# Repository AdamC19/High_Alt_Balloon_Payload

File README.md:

# High-Altitude Balloon Payload

These are the source files for my high-altitude balloon payload. 

Read more about this project and its development [on my website](http://acordingley.us/ke8itf/).

The primary goals of the payload are:
* Make measurements and collect data: 
    * GPS Location
    * Barometric pressure (second determination of altitude)
    * Temperature.
* Telemeter the data via the Amatuer Radio 2m band (144.39MHz).
* Log the data to non-volatile storage.
* Powered from NiMH batteries.

The primary goal of the real-time telemetry is to be able to receive GPS coordinates so that we can track the balloon and hopefully chase it and find it more easily. The payload will also include a self-contained camera to take pictures. 

## Hardware Block Diagrams
### Logical Overview

### Power Architecture

### 2m Radio Transmitter

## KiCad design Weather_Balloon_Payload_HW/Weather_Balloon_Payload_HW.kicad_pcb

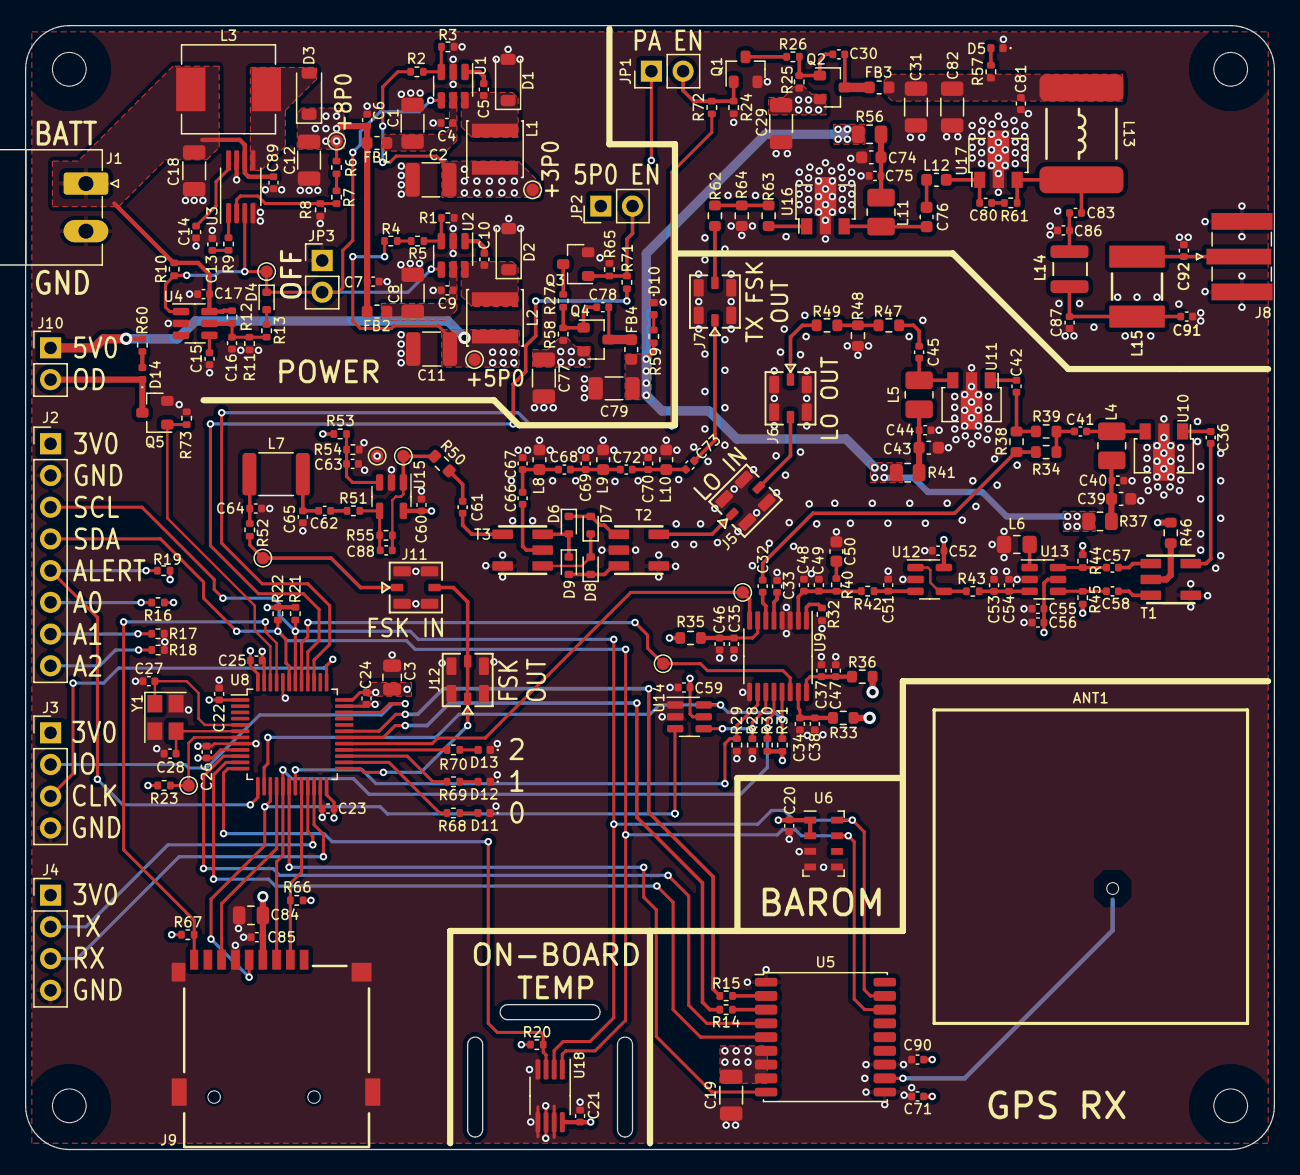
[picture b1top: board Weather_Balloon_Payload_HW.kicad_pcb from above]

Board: 4 copper layers, 100.0 x 90.0 mm, 254 parts (0 on the bottom side), 142 nets.

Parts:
ANT1: GP.1575.25.4.A.02; Taoglas_GP.1575.25.4.A.02
C1, C8, C12, C18, C19, C29, C31, C77, C79, C82: 10uF; C_1206_3216Metric
C2, C11: 22uF; C_1210_3225Metric
C3, C84: 4.7uF; C_0805_2012Metric
C4, C6, C7, C9, C17, C20, C21, C22, C23, C24, C25, C26, C38, C46, C47, C48, C49, C51, C52, C56, C59, C60, C61, C62, C63, C80, C85, C89: 0.1uF; C_0402_1005Metric
C5, C10, C14, C15: 0.01uF; C_0402_1005Metric
C13, C16: 1500pF; C_0402_1005Metric
C27, C28, C91, C92: 18pF; C_0402_1005Metric
C30, C34, C35, C36, C37, C40, C41, C42, C44, C45, C53, C55, C57, C58, C71, C75, C78, C81, C83, C90: 1000pF; C_0402_1005Metric
C32, C33, C54, C88: 100pF; C_0402_1005Metric
C39, C43, C50, C74, C76: 2.2uF; C_0603_1608Metric
C64, C65: 150pF; C_0402_1005Metric
C66, C73: 12pF; C_0402_1005Metric
C67, C69, C70: 110pF; C_0402_1005Metric
C68, C72: 4.7pF; C_0402_1005Metric
C86, C87: 10pF; C_0402_1005Metric
D1, D2, D3: LMBR130T1G; D_SOD-123
D4: 1N4148WT; D_SOD-523
D5, D10, D11, D12, D13, D14: BLUE; LED_0402_1005Metric
D6, D7, D8, D9: SMS3922-079LF; D_SOD-523
FB1, FB2, FB3, FB4: 120@100MHz; L_0603_1608Metric
H1, H2, H3, H4: M2.5; MountingHole_2.7mm_M2.5
J1: Conn_01x02; PhoenixContact_MC_1,5_2-G-3.81_1x02_P3.81mm_Horizontal
J2: Conn_01x08; PinHeader_1x08_P2.54mm_Vertical
J3, J4: Conn_01x04; PinHeader_1x04_P2.54mm_Vertical
J5, J6, J7, J11, J12: MM8430-2610; Connector_Murata_MM8430-2610RA1
J8: Conn_Coaxial; SMA_Amphenol_132384_EdgeMount
J9: XKTF-015-G; microSD_Card_Socket_Generic
J10: Conn_01x02; PinHeader_1x02_P2.54mm_Vertical
JP1, JP2, JP3: Jumper_2_Open; PinHeader_1x02_P2.54mm_Vertical
L1, L2: 4.7uH; L_Sunlord_SWPA4018S
L3: 10uH; L_Sunlord_MWSA0624S
L4, L5, L11: 120nH; L_1008_2520Metric_Pad1.43x2.20mm_HandSolder
L6: 180nH; L_0805_2012Metric_Pad1.15x1.40mm_HandSolder
L7: 15uH; L_1812_4532Metric
L8, L9, L10: 9.1nH; L_0603_1608Metric
L12: 5.6nH; L_0603_1608Metric
L13: 180nH; L_Coilcraft_2222SQ-181
L14: 47nH; L_Coilcraft_1111SQ-47N
L15: 68nH; L_Coilcraft_1515SQ-68N
Q1, Q3, Q5: Si2302; SOT-23
Q2, Q4: Si2301; SOT-23
R1, R8, R9, R12, R19, R20, R24, R25, R58, R65, R66, R67, R73: 10k; R_0402_1005Metric
R2, R4: 47k; R_0402_1005Metric
R3: 16.2k; R_0402_1005Metric
R5, R7, R23, R28, R29, R30, R31: 4.7k; R_0402_1005Metric
R6: 49.9k; R_0402_1005Metric
R10, R11: 100k; R_0402_1005Metric
R13: 1M; R_0402_1005Metric
R14, R15, R68, R69, R70: 100; R_0402_1005Metric
R16, R17, R18, R44, R45, R53, R54, R57, R71, R72: 1k; R_0402_1005Metric
R21, R22, R61: 1.5k; R_0402_1005Metric
R26, R27, R42, R55: 324; R_0402_1005Metric
R32: 5.1k; R_0402_1005Metric
R33, R35, R36, R46, R62, R63, R64: 0.0; R_0603_1608Metric
R34, R38, R39, R50: 49.9; R_0603_1608Metric
R37, R41, R56: 1.8; R_0805_2012Metric
R40, R43, R51, R52: 220; R_0402_1005Metric
R47, R49: 8.2; R_0603_1608Metric
R48: 150; R_0603_1608Metric
R59, R60: 470; R_0402_1005Metric
T1: CX2045LNLT; XFMR_Pulse_CX2049LNLT
T2, T3: TC2-72T+; XFMR_Mini-Circuits_TC2-72T+
TP1, TP2, TP3, TP4, TP5, TP6, TP7, TP8, TP9, TP10: TestPoint; TestPoint_Pad_D1.0mm
U1, U2: AP3211K; SOT-23-6
U3: ADP1612; MSOP-8_3x3mm_P0.65mm
U4: NCP308SN180T1G; SOT-23-6
U5: MAX-M8C; ublox_MAX
U6: MS5607-02BA; LGA-8_3x5mm_P1.25mm
U8: STM32F334C8Tx; LQFP-48_7x7mm_P0.5mm
U9: ADF4002BRUZ; TSSOP-16_4.4x5mm_P0.65mm
U10, U11, U16: PGA-105; SOT-89-3
U12: TLV9061; TSOT-23-5
U13: MAX2606; SOT-23-6
U14: TS5A3159ADBVR; SOT-23-6
U15: ADA4891-1; TSOT-23-5
U17: PHA13-HLN+; SOT-89-3
U18: MCP9808_MSOP; MSOP-8_3x3mm_P0.65mm
Y1: 12MHz; Crystal_SMD_3225-4Pin_3.2x2.5mm

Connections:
5P0_EN: R71.1, U8.40 (PB4)
+3V0: C2.1, C3.1, C19.2, C20.2, C21.2, C22.1, C23.1, C24.1, C25.1, C26.1, C52.1, C55.2, C56.1, C59.1, C60.1, C71.2, C84.1, C85.1, C90.2, J2.1, J3.1, J4.1, J9.4 (VDD), JP1.1 (A), JP2.1 (A), L1.2, R2.2, R16.2, R19.1, R20.1, R21.2, R22.2, R23.2, R30.2, R31.2, R33.2, R35.2, R36.2, R44.1, R45.1, R46.2, R53.1, R66.1, R67.1, TP3.1, U5.6 (V_BCKP), U5.7 (VCC_IO), U5.8 (VCC), U6.1 (VDD), U6.2 (PS), U8.1 (VBAT), U8.9 (VDDA), U8.24 (VDD), U8.36 (VDD), U8.48 (VDD), U12.5 (V+), U13.5 (VCC), U14.5 (V+), U15.5 (V+), U18.8 (V_{DD})
+5V: C11.1, C77.1, J10.1, L2.2, Q4.2 (S), R4.2, R58.1, R60.1, TP4.1
+8V: C6.1, C7.1, C12.1, C29.1, D3.1 (K), FB1.1, FB2.1, Q2.2 (S), R6.1, R25.1, TP2.1
/GPS and Barometer/GPS_ANT_CONN: ANT1.1 (A), U5.11 (RF_IN)
/GPS and Barometer/TSNS_EXT_A0: J2.6, R16.1
/GPS and Barometer/TSNS_EXT_A1: J2.7, R17.1
/GPS and Barometer/TSNS_EXT_A2: J2.8, R18.1
/GPS and Barometer/UART_GPS_MCU_PROT: R15.2, U5.2 (TXD)
/GPS and Barometer/UART_MCU_GPS_PROT: R14.2, U5.3 (RXD)
/LO Generator/AVDD: C35.2, C46.1, R35.1, U9.7 (AVDD)
/LO Generator/DVDD: C34.2, C38.1, R33.1, U9.15 (DVDD)
/LO Generator/LOOP_FILT_BUF: R43.2, U12.1, U12.4 (-)
/LO Generator/LOOP_FILT_OUT: C51.1, R42.1, U12.3 (+)
/LO Generator/LOOP_FILT_RC: C50.1, R40.1
/LO Generator/LO_AMP_IN: C42.1, U11.1
/LO Generator/LO_AMP_OUT: C45.2, L5.2, U11.3
/LO Generator/LO_INTER: J5.2 (OUT), J6.2 (OUT)
/LO Generator/LO_PREAMP: C42.2, R38.2, R39.1
/LO Generator/LO_T_ATTN: R47.2, R48.2, R49.1
/LO Generator/LO_T_ATTN_IN: C45.1, R47.1
/LO Generator/LO_T_ATTN_OUT: J6.1 (IN), R49.2
/LO Generator/PLL_CLK: R28.2, U9.11 (CLK), U14.4
/LO Generator/PLL_CP_OUT: C48.1, C49.1, R40.2, R42.2, U9.2 (CP)
/LO Generator/PLL_RFIN: C32.2, R34.1, R38.1
/LO Generator/PLL_RFINA: C32.1, U9.6 (RFINA)
/LO Generator/PLL_RFINB: C33.1, U9.5 (RFINB)
/LO Generator/PLL_RSET: R32.1, U9.1 (RSET)
/LO Generator/RF_SE: C36.2, T1.4
/LO Generator/RF_SE_AMP_IN: C36.1, U10.1
/LO Generator/RF_SE_AMP_O: C41.2, L4.2, U10.3
/LO Generator/RF_SE_AMP_PWR: C39.1, C40.2, L4.1, R37.1
/LO Generator/RF_SE_DIV_IN: C41.1, R34.2, R39.2
/LO Generator/VCO_BALUN_CT: R46.1, T1.2
/LO Generator/VCO_IND: L6.2, U13.1 (IND)
/LO Generator/VCO_OUT_N: C58.1, R45.2, U13.4 (OUT-)
/LO Generator/VCO_OUT_P: C57.1, R44.2, U13.6 (OUT+)
/LO Generator/VCO_TUNE: C53.1, C54.1, R43.1, U13.3 (TUNE)
/LO Generator/VP_3V3: C37.2, C47.1, R36.1, U9.16 (VP)
/Microcontroller/BUZZ_LED_LOW: D14.1 (K), J10.2, Q5.3 (D)
/Microcontroller/BUZZ_LED_R: D14.2 (A), R60.2
/Microcontroller/DBG_RX: J4.3, U8.22 (PB11)
/Microcontroller/DBG_TX: J4.2, U8.21 (PB10)
/Microcontroller/HRTIM_CHC1: J11.2 (OUT), J12.1 (IN), J12.2 (OUT), U8.25 (PB12)
/Microcontroller/LED_0: R68.2, U8.26 (PB13)
/Microcontroller/LED_0_A: D11.2 (A), R68.1
/Microcontroller/LED_1: R69.2, U8.27 (PB14)
/Microcontroller/LED_1_A: D12.2 (A), R69.1
/Microcontroller/LED_2: R70.2, U8.28 (PB15)
/Microcontroller/LED_2_A: D13.2 (A), R70.1
/Microcontroller/OSC_IN: C27.2, U8.5 (PF0), Y1.1
/Microcontroller/OSC_OUT: C28.2, U8.6 (PF1), Y1.3
/Microcontroller/STM_RSTB: R23.1, TP5.1, U8.7 (NRST)
/Microcontroller/SWDCLK: J3.3, U8.37 (PA14)
/Microcontroller/SWDIO: J3.2, U8.34 (PA13)
/Power/5P0_EN_LED: D10.2 (A), R59.2
/Power/5P0_EN_NFET_G: JP2.2 (B), Q3.1 (G), R65.1, R71.2
/Power/5P0_NFET_D: Q3.3 (D), R27.2
/Power/5P0_PFET_G: C78.1, Q4.1 (G), R27.1, R58.2
/Power/BATT_VIN: C17.1, C18.1, C89.2, J1.1, L3.1, R10.2, R12.1, U3.6 (VIN), U4.6 (VDD)
/Power/BST_3P0: C5.2, U1.1 (BS)
/Power/BST_5P0: C10.2, U2.1 (BS)
/Power/COMP_8P0: R9.1, U3.1 (COMP)
/Power/COMP_8P0_RC: C13.1, R9.2
/Power/FB_3P0: R2.1, R3.1, U1.3 (FB)
/Power/FB_5P0: R1.1, R5.2, U2.3 (FB)
/Power/FB_8P0: R7.1, R8.1, U3.2 (FB)
/Power/FB_R_5P0: R4.1, R5.1
/Power/FB_R_8P0: R6.2, R7.2
/Power/PA_EN_LED: D5.2 (A), R57.2
/Power/PA_EN_NFET_D: Q1.3 (D), R26.2
/Power/PA_EN_NFET_G: JP1.2 (B), Q1.1 (G), R24.1, R72.2
/Power/PA_PFET_G: C30.1, Q2.1 (G), R25.2, R26.1
/Power/SS_8P0: C14.1, U3.8 (SS)
/Power/SW_3P0: C5.1, D1.1 (K), L1.1, U1.6 (SW)
/Power/SW_5P0: C10.1, D2.1 (K), L2.1, U2.6 (SW)
/Power/SW_8P0: D3.2 (A), L3.2, U3.5 (SW)
/Power/SW_OUT_5P0: C78.2, FB4.1, Q4.3 (D)
/Power/SW_OUT_8P0: C30.2, FB3.1, Q2.3 (D)
/Power/UVLO_DLY_CAP: C15.1, U4.4 (CT)
/Power/UVLO_HYST: D4.2 (A), R13.2
/Power/UVLO_RSTB: D4.1 (K), JP3.2 (B), R10.1, TP1.1, U1.4 (EN), U2.4 (EN), U3.3 (EN), U4.1 (~RESET)
/Power/UVLO_SNS: C16.1, R11.2, R12.2, R13.1, U4.5 (SENSE)
/Power/VIN_3P0: C1.1, C4.1, FB1.2, U1.5 (IN)
/Power/VIN_5P0: C8.1, C9.1, FB2.2, U2.5 (IN)
/Transmitter/ANT_CONN: C92.2, J8.1 (In), L15.2
/Transmitter/ANT_MATCH: C83.1, C86.1, L14.1
/Transmitter/ANT_MATCH_2: C87.1, C91.2, L14.2, L15.1
/Transmitter/BASEBAND: C88.2, R50.2, R55.1, TP7.1, U15.1
/Transmitter/BASE_FILT_50: C61.1, R50.1
/Transmitter/DBM_1: D6.1 (K), D7.2 (A), T2.3
/Transmitter/DBM_2: D7.1 (K), D8.2 (A), T3.3
/Transmitter/DBM_3: D8.1 (K), D9.2 (A), T2.1
/Transmitter/DBM_4: D6.2 (A), D9.1 (K), T3.1
/Transmitter/MIX_FILT_1: C66.1, C67.1, C68.2, L8.1
/Transmitter/MIX_FILT_2: C68.1, C69.1, C72.2, L9.1
/Transmitter/MIX_FILT_3: C70.1, C72.1, C73.2, L10.1
/Transmitter/MIX_IF_OUT: C66.2, T3.2
/Transmitter/MIX_RF_IN: C61.2, T3.6
/Transmitter/PA_AMP_IN: C80.1, L12.2, U17.1
/Transmitter/PA_AMP_IN_1: C76.1, L12.1
/Transmitter/PA_RC: C80.2, R61.2
/Transmitter/PA_RF_DC: C83.2, L13.2, R61.1, U17.3
/Transmitter/PWM_FILT_AC: C62.2, R51.2
/Transmitter/PWM_FILT_IN: C64.2, L7.1, R52.1
/Transmitter/PWM_FILT_OUT: C62.1, C65.2, L7.2
/Transmitter/RF_TX_AMP_OUT: C76.2, L11.2, U16.3
/Transmitter/RF_TX_ATTN_OUT: R63.2, U16.1
/Transmitter/RF_TX_MOD: J7.2 (OUT), R62.1
/Transmitter/RF_TX_MOD_TP: C73.1, J7.1 (IN)
/Transmitter/RF_TX_T_ATTN: R62.2, R63.1, R64.2
/Transmitter/U15_INN: C88.1, R51.1, R55.2, U15.4 (-)
/Transmitter/U15_INP: C63.2, R53.2, R54.1, U15.3 (+)
BUZZ_LED_EN: Q5.1 (G), R73.1, U8.46 (PB9)
GND: C1.2, C2.2, C3.2, C4.2, C6.2, C7.2, C8.2, C9.2, C11.2, C12.2, C13.2, C14.2, C15.2, C16.2, C17.2, C18.2, C19.1, C20.1, C21.1, C22.2, C23.2, C24.2, C25.2, C26.2, C27.1, C28.1, C29.2, C31.2, C33.2, C34.1, C35.1, C37.1, C38.2, C39.2, C40.1, C43.2, C44.1, C46.2, C47.2, C48.2, C49.2, C50.2, C51.2, C52.2, C53.2, C54.2, C55.1, C56.2, C59.2, C60.2, C63.1, C64.1, C65.1, C67.2, C69.2, C70.2, C71.1, C74.2, C75.1, C77.2, C79.2, C81.1, C82.2, C84.2, C85.2, C86.2, C87.2, C89.1, C90.1, C91.1, C92.1, D1.2 (A), D2.2 (A), D5.1 (K), D10.1 (K), D11.1 (K), D12.1 (K), D13.1 (K), J1.2, J2.2, J3.4, J4.4, J5.3 (GND), J6.3 (GND), J7.3 (GND), J8.2 (Ext), J9.6 (VSS), J9.10 (SHIELD), J11.3 (GND), J12.3 (GND), JP3.1 (A), L6.1, L8.2, L9.2, L10.2, Q1.2 (S), Q3.2 (S), Q5.2 (S), R1.2, R3.2, R8.2, R11.1, R17.2, R18.2, R24.2, R28.1, R29.1, R32.2, R48.1, R54.2, R64.1, R65.2, R73.2, T1.6, T2.2, T2.6, T3.4, TP8.1, U1.2 (GND), U2.2 (GND), U3.4 (GND), U3.7 (FREQ), U4.2 (GND), U5.1 (GND), U5.10 (GND), U5.12 (GND), U6.3 (GND), U6.4 (CSB), U6.5 (CSB), U8.8 (VSSA), U8.23 (VSS), U8.35 (VSS), U8.44 (BOOT0), U8.47 (VSS), U9.3 (CPGND), U9.4 (AGND), U9.9 (DGND), U10.2 (GND), U11.2 (GND), U12.2 (V-), U13.2 (GND), U14.1, U14.2 (GND), U15.2 (V-), U16.2 (GND), U17.2 (GND), U18.4 (GND), U18.5 (A2), U18.6 (A1), U18.7 (A0), Y1.2, Y1.4
GPS_EXTINT: U5.5 (EXTINT), U8.11 (PA1)
GPS_PPS: U5.4 (TIMEPULSE), U8.10 (PA0)
GPS_RESETB: U5.9 (~RESET), U8.18 (PB0)
I2C_SCL: J2.3, R21.1, U5.17 (SCL), U6.8 (SCLK), U8.42 (PB6), U18.2 (SCL)
I2C_SDA: J2.4, R22.1, U5.16 (SDA), U6.7 (SDI/SDA), U8.43 (PB7), U18.1 (SDA)
LO_OUT: J5.1 (IN), T2.4
unnamed: C43.1, C44.2, L5.1, R41.1
unnamed: C57.2, T1.3
unnamed: C58.2, T1.1
unnamed: C74.1, C75.2, L11.1, R56.1
PA_EN: R72.1, U8.39 (PB3)
PLL_CE: R29.2, U8.19 (PB1), U9.10 (CE)
PLL_LE: R31.1, U8.14 (PA4), U9.13 (LE), U14.6
PLL_MUXOUT: TP6.1, U8.41 (PB5), U9.14 (MUXOUT)
PWM_SIGNAL: J11.1 (IN), R52.2, TP10.1
REF_12MHZ: TP9.1, U8.29 (PA8), U9.8 (REFIN)
SD_CS: J9.2 (DAT3/CD), R66.2, U8.20 (PB2)
SD_DET: J9.9 (DET), R67.2, U8.45 (PB8)
SPI_MISO: J9.7 (DAT0), U8.16 (PA6)
SPI_MOSI: J9.3 (CMD), R30.1, U8.17 (PA7), U9.12 (DATA)
SPI_SCLK: J9.5 (CLK), U8.15 (PA5), U14.3
TSNS_EXT_ALERT: J2.5, R19.2, U8.13 (PA3)
TSNS_INT_ALERT: R20.2, U8.12 (PA2), U18.3 (Alert)
UART_GPS_MCU: R15.1, U8.31 (PA10)
UART_MCU_GPS: R14.1, U8.30 (PA9)
V-5P0: C79.1, FB4.2, R37.2, R41.2, R56.2, R59.1
V-8P0_PA: C31.1, C81.2, C82.1, FB3.2, L13.1, R57.1

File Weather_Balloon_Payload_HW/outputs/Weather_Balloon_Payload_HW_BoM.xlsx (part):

Item | Qty | Reference(s) | Value | Footprint | Description | JLCPCB Part # | MFG | MFG_PN | Manufacturer | Mfr Part # | Mfr. Part # | Package Desc | Tolerance | Voltage Rating
1 | 1 | ANT1 | GP.1575.25.4.A.02 | Repowered_Antennas:Taoglas_GP.1575.25.4.A.02
2 | 10 | C1, C8, C12, C18, C19, C29, C31, C77, C79, C82 | 10uF | Capacitor_SMD:C_1206_3216Metric |  | C97952 |  |  | Murata Electronics |  | GRM31CR61C106KA88L | 1206 |  | 16V
3 | 2 | C2, C11 | 22uF | Capacitor_SMD:C_1210_3225Metric |  | C342660 |  |  | TDK |  | C3225X7R1C226KT000N | 1210 |  | 25V
4 | 2 | C3, C84 | 4.7uF | Capacitor_SMD:C_0805_2012Metric |  | C723891 |  |  | Murata Electronics |  | GRT21BR71C475KE13L | 805 |  | 16V
5 | 28 | C4, C6, C7, C9, C17, C20, C21, C22, C23, C24, C25, C26, C38, C46, C47, C48, C49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 | 0.1uF | Capacitor_SMD:C_0402_1005Metric | 50V 100nF X7R Â±10% 0402 Multilayer Ceramic Capacitors MLCC - SMD/SMT ROHS | C77020 |  |  | Murata Electronics | GRM155R71H104KE14D | GRM155R71H104KE14D | 402 |  | 50V
6 | 4 | C5, C10, C14, C15 | 0.01uF | Capacitor_SMD:C_0402_1005Metric | 50V 10nF X7R Â±10% 0402 Multilayer Ceramic Capacitors MLCC - SMD/SMT ROHS | C15195 |  |  | Samsung Electro-Mechanics |  | CL05B103KB5NNNC | 402 |  | 50V
7 | 2 | C13, C16 | 1500pF | Capacitor_SMD:C_0402_1005Metric |  | C107022 |  |  | YAGEO |  | CC0402KRX7R9BB152 | 402 |  | 50V
8 | 4 | C27, C28, C91, C92 | 18pF | Capacitor_SMD:C_0402_1005Metric |  | C106202 |  |  | YAGEO |  | CC0402JRNPO9BN180 | 402 |  | 50V
9 | 20 | C30, C34, C35, C36, C37, C40, C41, C42, C44, C45, C53, C55, C57, C58, C71, C75,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 | 1000pF | Capacitor_SMD:C_0402_1005Metric | 50V 1nF NP0 Â±5% 0402 Multilayer Ceramic Capacitors MLCC - SMD/SMT ROHS | C424332 |  |  | Darfon Elec |  | C1005NPO102JGT | 402 |  | 50V
10 | 4 | C32, C33, C54, C88 | 100pF | Capacitor_SMD:C_0402_1005Metric | 50V 100pF NP0 Â±5% 0402 Multilayer Ceramic Capacitors MLCC - SMD/SMT ROHS | C327785 |  |  | Walsin Tech Corp |  | MG15N101J500CT | 402 |  | 50V
11 | 5 | C39, C43, C50, C74, C76 | 2.2uF | Capacitor_SMD:C_0603_1608Metric | 16V 2.2uF X7S Â±10% 0603 Multilayer Ceramic Capacitors MLCC - SMD/SMT ROHS | C2859193 |  |  | SANYEAR |  | C0603X7S225K160NT | 603 |  | 16V
12 | 2 | C64, C65 | 150pF | Capacitor_SMD:C_0402_1005Metric | CAP CER 150pF 50V 5% C0G/NP0 0402 | C76951 |  |  | Murata Electronics |  | GRM1555C1H151JA01D | 402 |  | 50V
13 | 2 | C66, C73 | 12pF | Capacitor_SMD:C_0402_1005Metric | CAP CER 12pF 50V 2% C0G/NP0 0402 | C161305 |  |  | Murata Electronics |  | GJM1555C1H120GB01D | 402 |  | 50V
14 | 3 | C67, C69, C70 | 110pF | Capacitor_SMD:C_0402_1005Metric | CAP CER 110pF 50V 10% C0G/NP0 0402 | C185562 |  |  | Murata Electronics |  | GRM1555C1H111JA01D | 402 |  | 50V
15 | 2 | C68, C72 | 4.7pF | Capacitor_SMD:C_0402_1005Metric | CAP CER 4.7pF 50V C0G/NP0 0402 | C85856 |  |  | Murata Electronics |  | GCM1555C1H4R7CA16D | 402 |  | 50V
16 | 2 | C86, C87 | 10pF | Capacitor_SMD:C_0402_1005Metric | CAP CER 10pF 50V 1% C0G/NP0 0402 | C161145 |  |  | Murata Electronics |  | GCM1555C1H100FA16D | 402 |  | 50V
17 | 3 | D1, D2, D3 | LMBR130T1G | Diode_SMD:D_SOD-123 |  | C48974
18 | 1 | D4 | 1N4148WT | Diode_SMD:D_SOD-523 |  | C83482 |  |  |  |  | 1N4148WT-7
19 | 6 | D5, D10, D11, D12, D13, D14 | BLUE | LED_SMD:LED_0402_1005Metric |  | C131223 |  |  |  | 16-213/BHC-AN1P2/3T
20 | 4 | D6, D7, D8, D9 | SMS3922-079LF | Diode_SMD:D_SOD-523
21 | 4 | FB1, FB2, FB3, FB4 | 120@100MHz | Inductor_SMD:L_0603_1608Metric | 50mÎ© Â±25% 120Î©@100MHz 0603 Ferrite Beads ROHS | C14709 |  |  | Murata Electronics |  | BLM18PG121SN1D
23 | 1 | J1 | Conn_01x02 | Connector_Phoenix_MC:PhoenixContact_MC_1,5_2-G-3.81_1x02_P3.81mm_Horizontal
26 | 5 | J5, J6, J7, J11, J12 | MM8430-2610 | Repowered_Connectors:Connector_Murata_MM8430-2610RA1 | CONN SWD RCPT W/ SWITCH 50 OHM SMD | C91634 | Murata | MM8430-2610RA1 | Murata |  | MM8430-2610RB3
27 | 1 | J8 | Conn_Coaxial | Repowered_Connectors:SMA_Amphenol_132384_EdgeMount
28 | 1 | J9 | XKTF-015-G | Repowered_Connectors:microSD_Card_Socket_Generic | 2mm Gold Deck MicroSD card (TF card) 260â„ƒ Copper Alloy Self bomb SMD SD Card 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 | C1121874 |  |  | XKB Connectivity |  | XKTF-015-G
30 | 2 | L1, L2 | 4.7uH | Inductor_SMD:L_Sunlord_SWPA4018S |  | C60117 |  |  | Sunlord |  | SWPA4018S4R7MT
31 | 1 | L3 | 10uH | Inductor_SMD:L_Sunlord_MWSA0624S |  | C408435 |  |  | Sunlord |  | MWSA0624S-100MT
32 | 3 | L4, L5, L11 | 120nH | Inductor_SMD:L_1008_2520Metric_Pad1.43x2.20mm_HandSolder |  | C703706 |  |  |  |  | LQW2UASR12G00L
33 | 1 | L6 | 180nH | Inductor_SMD:L_0805_2012Metric_Pad1.15x1.40mm_HandSolder |  |  |  |  |  |  | 0805HP-181XJRC
34 | 1 | L7 | 15uH | Inductor_SMD:L_1812_4532Metric | 500mA 15uH Â±5% 1.2Î© 1812 Inductors (SMD) ROHS | C394123 |  |  |  |  | FHW1812IF150JST
35 | 3 | L8, L9, L10 | 9.1nH | Inductor_SMD:L_0603_1608Metric | 650mA 9.1nH 110mÎ© 0603 Inductors (SMD) ROHS | C701193 |  |  |  |  | LQW18AN9N1C00D
36 | 1 | L12 | 5.6nH | Inductor_SMD:L_0603_1608Metric | 750mA 5.6nH 82mÎ© 0603 Inductors (SMD) ROHS | C98081 |  |  |  |  | LQW18AN5N6C00D
37 | 1 | L13 | 180nH | Repowered_Inductors_SMD:L_Coilcraft_2222SQ-181 |  |  |  |  |  |  | 2222SQ-181GEC
38 | 1 | L14 | 47nH | Repowered_Inductors_SMD:L_Coilcraft_1111SQ-47N |  |  |  |  |  |  | 1111SQ-47NJEC
39 | 1 | L15 | 68nH | Repowered_Inductors_SMD:L_Coilcraft_1515SQ-68N |  |  |  |  |  |  | 1515SQ-68NJEC
40 | 3 | Q1, Q3, Q5 | Si2302 | Repowered_TO-SOT-SMD:SOT-23 |  | C2891732 |  |  | YONGYUTAI |  | SI2302
41 | 2 | Q2, Q4 | Si2301 | Repowered_TO-SOT-SMD:SOT-23 |  | C2891731 |  |  | YONGYUTAI |  | SI2301
42 | 13 | R1, R8, R9, R12, R19, R20, R24, R25, R58, R65, R66, R67, R73 | 10k | Resistor_SMD:R_0402_1005Metric | 62.5mW Thick Film Resistors Â±0.5% 10.2kÎ© 0402 Chip Resistor - Surface Mount R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 | C303730 |  |  | RALEC |  | RTT021022DTH | 402 | 0.01
43 | 2 | R2, R4 | 47k | Resistor_SMD:R_0402_1005Metric | 62.5mW Thin Film Resistor Â±25ppm/â„ƒ Â±1% 47kÎ© 0402 Chip | C284586 |  |  | Viking Tech |  | ARG02FTC4702 | 402 | 0.01
44 | 1 | R3 | 16.2k | Resistor_SMD:R_0402_1005Metric | 62.5mW Thick Film Resistors Â±100ppm/â„ƒ Â±1% 16.2kÎ© 0402 Chip | C138050 |  |  | YAGEO |  | RC0402FR-0716K2L | 402 | 0.01
45 | 7 | R5, R7, R23, R28, R29, R30, R31 | 4.7k | Resistor_SMD:R_0402_1005Metric |  | C103055 |  |  | RALEC |  | RTT024701FTH | 402 | 0.01
46 | 1 | R6 | 49.9k | Resistor_SMD:R_0402_1005Metric | 62.5mW Thin Film Resistor Â±25ppm/â„ƒ Â±1% 49.9kÎ© 0402 Chip | C284595 |  |  | Viking Tech |  | ARG02FTC4992 | 402 | 0.01
47 | 2 | R10, R11 | 100k | Resistor_SMD:R_0402_1005Metric | RES SMD 100K 1% 62.5mW 0402 | C279979 |  |  | Viking Tech |  | CR-02FL6--100K | 402 | 0.01
48 | 1 | R13 | 1M | Resistor_SMD:R_0402_1005Metric |  |  |  |  |  |  |  | 402 | 0.01
49 | 5 | R14, R15, R68, R69, R70 | 100 | Resistor_SMD:R_0402_1005Metric | RES SMD 100 1% 62.5mW 0402 | C409720 |  |  | Viking Tech |  | AS02FTE1000 | 402 | 0.01
50 | 10 | R16, R17, R18, R44, R45, R53, R54, R57, R71, R72 | 1k | Resistor_SMD:R_0402_1005Metric |  | C153104 |  |  | TA-I Tech |  | RM04JTN102 | 402 | 0.01
51 | 3 | R21, R22, R61 | 1.5k | Resistor_SMD:R_0402_1005Metric | 62.5mW Thick Film Resistors Â±100ppm/â„ƒ Â±5% 1.5kÎ© 0402 Chip | C144726 |  |  | YAGEO |  | AC0402JR-071K5L | 402 | 0.01
52 | 4 | R26, R27, R42, R55 | 324 | Resistor_SMD:R_0402_1005Metric | 62.5mW Thick Film Resistors Â±100ppm/â„ƒ Â±1% 324Î© 0402 Chip | C423191 |  |  | UNI-ROYAL(Uniroyal Elec) |  | 0402WGF3240TCE | 402 | 0.01
53 | 1 | R32 | 5.1k | Resistor_SMD:R_0402_1005Metric |  | C163833 |  |  | Walsin Tech Corp |  | WR04X5101FTL | 402 | 0.01
54 | 6 | R33, R35, R36, R46, R62, R63 | 0 | Resistor_SMD:R_0603_1608Metric | 100mW Thick Film Resistors Â±5% 0Î© 0603 Chip Resistor - Surface Mount ROHS | C429617 |  |  | Ever Ohms Tech |  | CR0603J0R00P05Z | 603
55 | 4 | R34, R38, R39, R50 | 49.9 | Resistor_SMD:R_0603_1608Metric |  | C114625 |  |  | YAGEO |  | RC0603FR-0749R9L | 603 | 0.01
56 | 3 | R37, R41, R56 | 1.8 | Resistor_SMD:R_0805_2012Metric |  | C384139 |  |  | Walsin Tech Corp |  | WR08X1R8JTL | 805 | 0.01
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
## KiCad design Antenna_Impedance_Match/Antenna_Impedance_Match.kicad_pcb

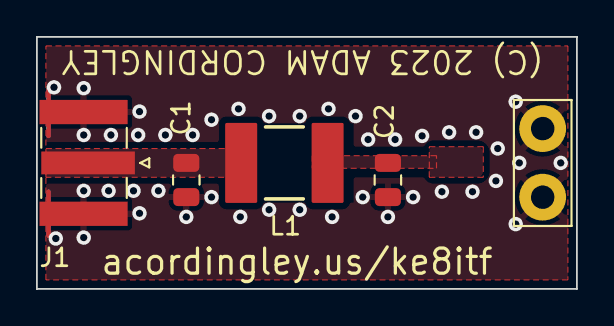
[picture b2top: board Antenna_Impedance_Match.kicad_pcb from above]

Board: 2 copper layers, 30.0 x 14.0 mm, 5 parts (0 on the bottom side), 3 nets.

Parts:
C1, C2: 18pF; C_0805_2012Metric
J1: Conn_Coaxial; SMA_Amphenol_132384_EdgeMount
L1: 68nH; L_Coilcraft_1515SQ-68N
TP2: TestPoint; TestPoint_Bridge_Pitch3.81mm_Drill1.3mm

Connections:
/RF_50_SE: C1.2, J1.1 (In), L1.1
/RF_75_SE: C2.2, L1.2
GND: C1.1, C2.1, J1.2 (Ext), TP2.1

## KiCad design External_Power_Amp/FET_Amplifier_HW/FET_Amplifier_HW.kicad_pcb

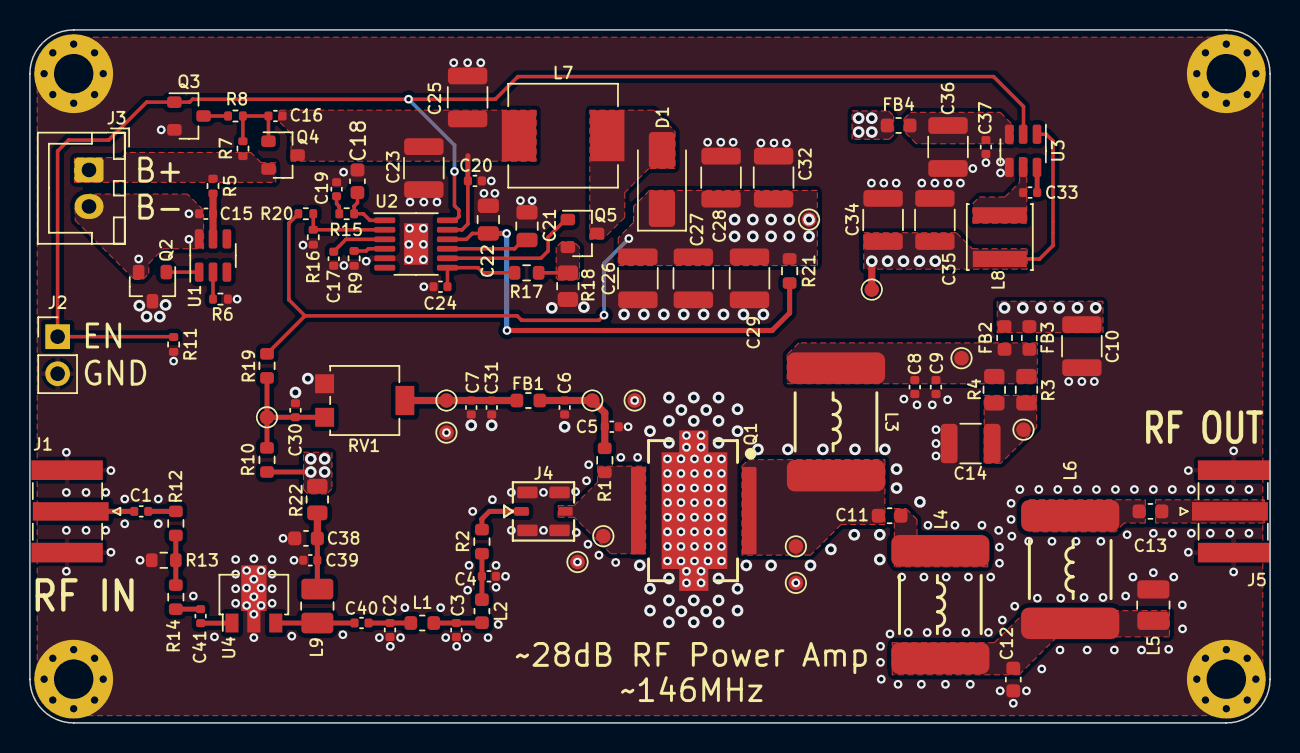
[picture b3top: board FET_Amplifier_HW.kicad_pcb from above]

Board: 4 copper layers, 85.0 x 47.5 mm, 110 parts (0 on the bottom side), 49 nets.

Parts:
C1, C5, C8, C16, C24, C31, C39, C40, C41: 1000pF; C_0402_1005Metric
C2: 5.6pF; C_0402_1005Metric
C3: 12pF; C_0402_1005Metric
C4: 3.6pF; C_0402_1005Metric
C6, C7, C9, C15, C17, C20, C30, C33, C37: 0.1uF; C_0402_1005Metric
C10, C14, C36: 10uF; C_1210_3225Metric
C11, C13: 6.8pF; C_0603_1608Metric
C12, C18: 100pF; C_0603_1608Metric
C19: 0.022uF; C_0402_1005Metric
C21: 4.7uF; C_0805_2012Metric
C22: 1uF; C_0805_2012Metric
C23, C25, C26, C27, C28, C29, C32, C34, C35: 22uF; C_1210_3225Metric
C38: 2.2uF; C_0603_1608Metric
D1: SS54SMA; D_SMA
FB1, FB2, FB3, FB4: 330@100MHz; L_0603_1608Metric
H1, H2, H3, H4: M2.5; MountingHole_2.7mm_M2.5_Pad_Via
J1, J5: Conn_Coaxial; SMA_Amphenol_132384_EdgeMount
J2: Conn_01x02; PinHeader_1x02_P2.54mm_Vertical
J3: JST-XH; JST_XH_B2B-XH-A_1x02_P2.50mm_Vertical
J4: MM8430-2610; Connector_Murata_MM8430-2610RA1
L1: 18nH; L_0603_1608Metric
L2: 16nH; L_0603_1608Metric
L3, L4, L6: 180nH; L_Coilcraft_2222SQ-181
L5: 10nH; L_1008_2520Metric
L7: 10uH; L_Sunlord_MWSA0624S
L8: 4.7uH; L_Sunlord_SWPA4018S
L9: 120nH; L_1008_2520Metric_Pad1.43x2.20mm_HandSolder
NT1: NetTie_2; NetTie-2_SMD_Pad0.25mm
Q1: BLP15H9S100GZ; SOT-1483-1
Q2, Q5: DMN3023L; SOT-23
Q3: Si2302; SOT-23
Q4: DMP2035U-7; SOT-23
R1: 49.9; R_0603_1608Metric
R2, R10, R12, R13, R14, R17, R19, R21: 0.0; R_0603_1608Metric
R3, R4: 1.0; R_0805_2012Metric
R5, R8: 330; R_0402_1005Metric
R6: 1k; R_0402_1005Metric
R7, R11, R16: 10k; R_0402_1005Metric
R9: 24.9k; R_0402_1005Metric
R15: 7.5k; R_0402_1005Metric
R18: 0.005; R_0805_2012Metric
R20: 100k; R_0402_1005Metric
R22: 1.8; R_0805_2012Metric
RV1: 10k; Potentiometer_Bourns_3314G_Vertical
TP1, TP2, TP3, TP4, TP5, TP6, TP7, TP8, TP9, TP10, TP11, TP12, TP13: TestPoint; TestPoint_Pad_D1.0mm
U1: AP9101CK6; SOT-23-6
U2: LT3759xMSE; MSOP-12-1EP_3x4mm_P0.65mm_EP1.65x2.85mm
U3: AP63205WU-7; TSOT-23-6
U4: PGA-105; SOT-89-3

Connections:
/BIAS: C7.1, C31.1, FB1.1, RV1.2, TP1.1
/BIAS_FILT: C5.1, C6.1, FB1.2, R1.2, TP2.1
/COAX_TP_IN: J4.1 (IN), R2.2
/C_DAMP: C14.2, R3.2, R4.2, TP7.1
/FET_DRAIN: C11.2, L3.2, Q1.1 (D), TP6.1
/FET_GATE: J4.2 (OUT), Q1.2 (G), R1.1, TP3.1
/FET_PWR_FILT: C8.1, C9.1, FB2.1, FB3.1, L3.1, R3.1, R4.1, TP4.1
/IN_FILT_FINAL: C4.1, L2.2, R2.1
/IN_FILT_LC: C3.1, L1.2, L2.1
/OUT_FILT_1: C11.1, L4.1
/OUT_FILT_2: C12.1, L4.2, L5.1, L6.1
/OUT_FILT_3: C13.2, L6.2
/Power Conversion/BATT_GND: C15.1, J3.2, Q2.2 (S), U1.6 (VSS)
/Power Conversion/BOOST_CS: Q5.2 (S), R17.1, R18.2
/Power Conversion/BOOST_DRV: C22.1, R21.2, U2.10 (DRIVE)
/Power Conversion/BOOST_EN: J2.1, Q3.1 (G), R11.1, U2.12 (EN/UVLO), U3.2 (EN)
/Power Conversion/BOOST_FB: R16.1, R20.1, U2.2 (FBX)
/Power Conversion/BOOST_GATE: Q5.1 (G), U2.8 (GATE)
/Power Conversion/BOOST_ISNS: C24.1, R17.2, U2.7 (SENSE)
/Power Conversion/BOOST_RT: R9.2, U2.4 (RT)
/Power Conversion/BOOST_SS: C17.1, U2.3 (SS)
/Power Conversion/BOOST_SW: D1.2 (A), L7.2, Q5.3 (D)
/Power Conversion/BOOST_VCOMP: C18.1, R15.2, U2.1 (VC)
/Power Conversion/BOOST_VIN: C16.1, C20.2, C23.1, C25.1, L7.1, Q4.3 (D), U2.11 (VIN)
/Power Conversion/BUCK_BST: C33.2, U3.6 (BST)
/Power Conversion/BUCK_FB: NT1.1, U3.1 (FB)
/Power Conversion/BUCK_SW: C33.1, L8.1, U3.5 (SW)
/Power Conversion/BUCK_VIN: C36.2, C37.1, FB4.2, U3.3 (IN)
/Power Conversion/INTVCC: C21.1, U2.9 (INTVCC)
/Power Conversion/PROT_DO: Q2.1 (G), U1.1 (DO)
/Power Conversion/PROT_VDD: C15.2, R5.2, U1.5 (VDD)
/Power Conversion/PROT_VM: R6.1, U1.2 (VM)
/Power Conversion/VC_RC: C19.1, R15.1
/Power Conversion/VIN_EXT: J3.1, Q4.2 (S), R5.1, R7.1
/Power Conversion/VIN_SW_G: C16.2, Q4.1 (G), R7.2, R8.1
/Power Conversion/VIN_SW_NFET_D: Q3.3 (D), R8.2
/RF_AMP_IN: C41.1, U4.1
/RF_AMP_OUT: C40.2, L9.2, U4.3
/RF_IN: C2.1, C40.1, L1.1
/RF_IN_EXT: C1.2, J1.1 (In)
/RF_OUT_EXT: C13.1, J5.1 (In)
/TEE_ATTN: R12.2, R13.2, R14.1
/TEE_ATTN_IN: C1.1, R12.1
/TEE_OUT: C41.2, R14.2
/V-VCC_BIAS: C30.1, R10.1, R19.1, RV1.3, TP9.1
BOOST_VOUT: C10.2, C26.1, C27.1, C28.1, C29.1, C32.1, D1.1 (K), FB2.2, FB3.2, FB4.1, R19.2, R20.2, R21.1, TP5.1
GND: C2.2, C3.2, C4.2, C5.2, C6.2, C7.2, C8.2, C9.2, C10.1, C12.2, C14.1, C17.2, C18.2, C19.2, C20.1, C21.2, C22.2, C23.2, C24.2, C25.2, C26.2, C27.2, C28.2, C29.2, C30.2, C31.2, C32.2, C34.2, C35.2, C36.1, C37.2, C38.2, C39.1, H1.1, H2.1, H3.1, H4.1, J1.2 (Ext), J2.2, J4.3 (GND), J5.2 (Ext), L5.2, Q1.3 (S), Q2.3 (D), Q3.2 (S), R6.2, R9.1, R11.2, R13.1, R16.2, R18.1, RV1.1, TP8.1, TP11.1, TP12.1, TP13.1, U2.5 (SYNC), U2.13 (GND), U3.4 (GND), U4.2 (GND)
unnamed: C38.1, C39.2, L9.1, R22.1
V-5P0: C34.1, C35.1, L8.2, NT1.2, R10.2, R22.2, TP10.1

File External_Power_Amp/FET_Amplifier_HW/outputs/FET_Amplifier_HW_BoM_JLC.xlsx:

Item | Qty | Designator | Comment | Footprint | Description | JLCPCB Part # | Manufacturer | Mfr. Part #
1 | 8 | C1, C5, C8, C16, C31, C39, C40, C41 | 1000pF | Capacitor_SMD:C_0402_1005Metric | CAP SMD 1000pF 10% 50V X7R 0603 | C1588 | Samsung Electro-Mechanics | CL10B102KB8NNNC
2 | 1 | C2 | 5.6pF | Capacitor_SMD:C_0402_1005Metric | CAP SMD 5.6pF 10% 50V NPO/C0G 0402 | C88895 | Murata Electronics | GJM1555C1H5R6CB01D
3 | 1 | C3 | 12pF | Capacitor_SMD:C_0402_1005Metric | CAP SMD 12pF 10% 50V NPO/C0G 0402 | C106201 | YAGEO | CC0402JRNPO9BN120
4 | 1 | C4 | 3.6pF | Capacitor_SMD:C_0402_1005Metric | CAP SMD 3.6pF 10% 50V NPO/C0G 0402 | C161321 | Murata Electronics | GJM1555C1H3R6WB01D
5 | 9 | C6, C7, C9, C15, C17, C20, C30, C33, C37 | 0.1uF | Capacitor_SMD:C_0402_1005Metric | 50V 100nF X7R Â±10% 0402 Multilayer Ceramic Capacitors MLCC - SMD/SMT ROHS | C77020 | Murata Electronics | GRM155R71H104KE14D
6 | 3 | C10, C14, C36 | 10uF | Capacitor_SMD:C_1210_3225Metric | CAP SMD 10uF 50V 10% X7R 1210 | C386167 | Taiyo Yuden | UMK325AB7106KM-T
7 | 2 | C11, C13 | 6.8pF | Capacitor_SMD:C_0603_1608Metric | CAP SMD 6.8pF 10% 50V NP0/C0G 0603 | C1679 | FH (Guangdong Fenghua Advanced Tech) | 0603CG6R8C500NT
8 | 2 | C12, C18 | 100pF | Capacitor_SMD:C_0603_1608Metric | CAP SMD 100pF 10% 50V NP0/C0G 0603 | C14858 | Samsung Electro-Mechanics | CL10C101JB8NNNC
9 | 1 | C19 | 0.022uF | Capacitor_SMD:C_0402_1005Metric | CAP SMD 22nF 10% 50V X7R 0603 | C21122 | Samsung Electro-Mechanics | CL10B223KB8NNNC
10 | 1 | C21 | 4.7uF | Capacitor_SMD:C_0805_2012Metric | CAP CER 4.7UF 16V X5R 0805 | C1779 | Samsung Electro-Mechanics | CL21A475KAQNNNE
11 | 1 | C22 | 1uF | Capacitor_SMD:C_0805_2012Metric | CAP SMD 1uF 10% 50V X5R 0603 | C15849 | Samsung Electro-Mechanics | CL10A105KB8NNNC
12 | 9 | C23, C25, C26, C27, C28, C29, C32, C34, C35 | 22uF | Capacitor_SMD:C_1210_3225Metric | CAP CER 22uF 20% 25V X5R 1210 | C342660 | TDK | C3225X7R1C226KT000N
13 | 1 | C24 | 1000pF | Capacitor_SMD:C_0402_1005Metric | CAP SMD 1000pF 10% 50V X7R 0603 | C1588 | Samsung Electro-Mechanics | CL10B102KB8NNNC
14 | 1 | C38 | 2.2uF | Capacitor_SMD:C_0603_1608Metric | 16V 2.2uF X7S Â±10% 0603 Multilayer Ceramic Capacitors MLCC - SMD/SMT ROHS | C2859193 | SANYEAR | C0603X7S225K160NT
15 | 1 | D1 | SS54SMA | Diode_SMD:D_SMA | 40V 550mV@3A 5A SMA Schottky | C511853 |  | SS54SMA
16 | 4 | FB1, FB2, FB3, FB4 | 330@100MHz | Inductor_SMD:L_0603_1608Metric | 70mÎ© Â±25% 330Î©@100MHz 0603 Ferrite Beads ROHS | C710391 | Murata Electronics | BLM18SG331TZ1D
21 | 1 | J4 | MM8430-2610 | Repowered_Connectors:Connector_Murata_MM8430-2610RA1 | CONN SWD RCPT W/ SWITCH 50 OHM SMD | C91634 | Murata | MM8430-2610RB3
22 | 1 | L1 | 18nH | Inductor_SMD:L_0603_1608Metric |  | C1332655 |  | LQW18AN18NJ80D
23 | 1 | L2 | 16nH | Inductor_SMD:L_0603_1608Metric |  | C237581 |  | LQW18AN16NG00D
26 | 1 | L7 | 10uH | Inductor_SMD:L_Sunlord_MWSA0624S |  | C408435 | Sunlord | MWSA0624S-100MT
27 | 1 | L8 | 4.7uH | Inductor_SMD:L_Sunlord_SWPA4018S |  | C60117 | Sunlord | SWPA4018S4R7MT
28 | 1 | L9 | 120nH | Inductor_SMD:L_1008_2520Metric_Pad1.43x2.20mm_HandSolder |  | C703706 |  | LQW2UASR12G00L
30 | 2 | Q2, Q5 | DMN3023L | Repowered_TO-SOT-SMD:SOT-23 |  | C443825 | Diodes Incorporated | DMN3023L-7
31 | 1 | Q3 | Si2302 | Repowered_TO-SOT-SMD:SOT-23 |  | C2891732 | YONGYUTAI | SI2302
32 | 1 | Q4 | DMP2035U-7 | Repowered_TO-SOT-SMD:SOT-23 | MOSFET P-CH 20V 3.6A SOT23-3 | C110499 | Diodes Incorporated | DMP2035U-7
33 | 1 | R1 | 49.9 | Resistor_SMD:R_0603_1608Metric | RES SMD 49.9 1% 100mW 0603 | C23185 | UNI-ROYAL(Uniroyal Elec) | 0603WAF499JT5E
34 | 6 | R2, R10, R12, R14, R17, R21 | 0 | Resistor_SMD:R_0603_1608Metric | 100mW Â±1% 0Î© 0603 Chip Resistor - Surface Mount ROHS | C192909 | YAGEO | AF0603FR-070RL
35 | 2 | R3, R4 | 1 | Resistor_SMD:R_0805_2012Metric |  | C144579 | YAGEO | AC0805FR-071RL
36 | 2 | R5, R8 | 330 | Resistor_SMD:R_0402_1005Metric |  | C25104 | UNI-ROYAL(Uniroyal Elec) | 0402WGF3300TCE
37 | 1 | R6 | 1k | Resistor_SMD:R_0402_1005Metric |  | C11702 | UNI-ROYAL(Uniroyal Elec) | 0402WGF1001TCE
38 | 3 | R7, R11, R16 | 10k | Resistor_SMD:R_0402_1005Metric | 62.5mW Thick Film Resistors Â±0.5% 10.2kÎ© 0402 Chip Resistor - Surface Mount R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 | C303730 | RALEC | RTT021022DTH
39 | 1 | R9 | 24.9k | Resistor_SMD:R_0402_1005Metric |  | C138027 | YAGEO | RC0402FR-0724K9L
40 | 2 | R13, R19 | 0 | Resistor_SMD:R_0603_1608Metric | 100mW Â±1% 0Î© 0603 Chip Resistor - Surface Mount ROHS | C192909 | YAGEO | AF0603FR-070RL
41 | 1 | R15 | 7.5k | Resistor_SMD:R_0402_1005Metric |  | C25918 | UNI-ROYAL(Uniroyal Elec) | 0402WGF7501TCE
42 | 1 | R18 | 5.0000000000000001E-3 | Resistor_SMD:R_0805_2012Metric |  | C163091 | TA-I Tech | RLM10FTSMR005
43 | 1 | R20 | 100k | Resistor_SMD:R_0402_1005Metric |  | C25741 | UNI-ROYAL(Uniroyal Elec) | 0402WGF1003TCE
44 | 1 | R22 | 1.8 | Resistor_SMD:R_0805_2012Metric |  | C384139 | Walsin Tech Corp | WR08X1R8JTL
45 | 1 | RV1 | 10k | Potentiometer_SMD:Potentiometer_Bourns_3314G_Vertical |  | C780220 | Bourns | 3314G-1-103E
47 | 1 | U1 | AP9101CK6 | Package_TO_SOT_SMD:SOT-23-6 |  | C151339 |  | AP9101CK6-ADTRG1
49 | 1 | U3 | AP63205WU-7 | Package_TO_SOT_SMD:TSOT-23-6 |  | C2071056 |  | AP63205WU-7
50 | 1 | U4 | PGA-105 | Package_TO_SOT_SMD:SOT-89-3 |  | C879859

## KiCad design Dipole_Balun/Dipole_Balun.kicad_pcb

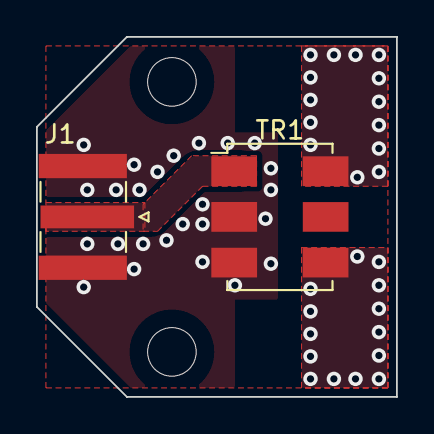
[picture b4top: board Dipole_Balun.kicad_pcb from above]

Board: 2 copper layers, 20.0 x 20.0 mm, 4 parts (0 on the bottom side), 2 nets, no tracks yet.

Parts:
H1, H2: M2.5; MountingHole_2.7mm_M2.5
J1: Conn_Coaxial; SMA_Amphenol_132384_EdgeMount
TR1: ADT1.5-1; Mini-Circuits_CD542_H2.84mm

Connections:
/RF_IN: J1.1 (In), TR1.1
GND: J1.2 (Ext), TR1.2, TR1.3

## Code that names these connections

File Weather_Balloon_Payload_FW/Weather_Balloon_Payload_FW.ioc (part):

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Mcu.Name=STM32F334C(4-6-8)Tx
Mcu.Package=LQFP48
Mcu.UserName=STM32F334C8Tx
PA0.GPIOParameters=GPIO_PuPd,GPIO_Label
PA0.GPIO_Label=GPS_PPS
PA0.GPIO_PuPd=GPIO_PULLDOWN
PA0.Signal=GPXTI0
PA1.GPIOParameters=GPIO_Label
PA1.GPIO_Label=GPS_EXTINT
PA1.Signal=GPXTI1
PA10.Mode=Asynchronous
PA10.Signal=USART1_RX
PA13.Mode=Serial_Wire
PA13.Signal=SYS_JTMS-SWDIO
PA14.Mode=Serial_Wire
PA14.Signal=SYS_JTCK-SWCLK
PA2.GPIOParameters=GPIO_PuPd,GPIO_Label,GPIO_ModeDefaultEXTI
PA2.GPIO_Label=TSENS_INT_ALERT
PA2.GPIO_ModeDefaultEXTI=GPIO_MODE_IT_FALLING
PA2.GPIO_PuPd=GPIO_PULLUP
PA2.Signal=GPXTI2
PA3.GPIOParameters=GPIO_PuPd,GPIO_Label,GPIO_ModeDefaultEXTI
PA3.GPIO_Label=TSNS_EXT_ALERT
PA3.GPIO_ModeDefaultEXTI=GPIO_MODE_IT_FALLING
PA3.GPIO_PuPd=GPIO_PULLUP
PA3.Signal=GPXTI3
PA4.GPIOParameters=GPIO_Speed,GPIO_Label
PA4.GPIO_Label=PLL_LE
PA4.GPIO_Speed=GPIO_SPEED_FREQ_MEDIUM
PA4.Signal=GPIO_Output
PA5.Mode=Full_Duplex_Master
PA5.Signal=SPI1_SCK
PA6.Mode=Full_Duplex_Master
PA6.Signal=SPI1_MISO
PA7.Mode=Full_Duplex_Master
PA7.Signal=SPI1_MOSI
PA8.Mode=Clock-out
PA8.Signal=RCC_MCO
PA9.Mode=Asynchronous
PA9.Signal=USART1_TX
PB0.GPIOParameters=GPIO_Label
PB0.GPIO_Label=GPS_RESETB
PB0.Signal=GPIO_Output
PB1.GPIOParameters=GPIO_Label
PB1.GPIO_Label=PLL_CE
PB1.Signal=GPIO_Output
PB10.Mode=Asynchronous
PB10.Signal=USART3_TX
PB11.Mode=Asynchronous
PB11.Signal=USART3_RX
PB12.Mode=Output_TC1
PB12.Signal=HRTIM1_CHC1
PB13.GPIOParameters=GPIO_Label
PB13.GPIO_Label=LED_0
PB13.Signal=GPIO_Output
PB14.GPIOParameters=GPIO_Label
PB14.GPIO_Label=LED_1
PB14.Signal=GPIO_Output
PB15.GPIOParameters=GPIO_Label
PB15.GPIO_Label=LED_2
PB15.Signal=GPIO_Output
PB2.GPIOParameters=GPIO_Label
PB2.GPIO_Label=SD_CS
PB2.Signal=GPIO_Output
PB3.GPIOParameters=GPIO_Label
PB3.GPIO_Label=PA_EN
PB3.Signal=GPIO_Output
PB4.GPIOParameters=GPIO_Label
PB4.GPIO_Label=EN_5P0
PB4.Signal=GPIO_Output
PB5.GPIOParameters=GPIO_PuPd,GPIO_Label
PB5.GPIO_Label=PLL_MUXOUT
PB5.GPIO_PuPd=GPIO_PULLDOWN
PB5.Signal=GPIO_Input
PB6.Mode=I2C
PB6.Signal=I2C1_SCL
PB7.Mode=I2C
PB7.Signal=I2C1_SDA
PB8.GPIOParameters=GPIO_PuPd,GPIO_Label
PB8.GPIO_Label=SD_DET
PB8.GPIO_PuPd=GPIO_PULLUP
PB8.Signal=GPIO_Input
PB9.GPIOParameters=GPIO_Label
PB9.GPIO_Label=BUZZ_LED_EN
PB9.Signal=GPIO_Output
PF0\ /\ OSC_IN.Mode=HSE-External-Oscillator
PF0\ /\ OSC_IN.Signal=RCC_OSC_IN
PF1\ /\ OSC_OUT.Mode=HSE-External-Oscillator
PF1\ /\ OSC_OUT.Signal=RCC_OSC_OUT
RCC.HSEPLLFreq_Value=12000000
RCC.HSE_VALUE=12000000
RCC.SYSCLKFreq_VALUE=72000000
RCC.SYSCLKSourceVirtual=RCC_SYSCLKSOURCE_PLLCLK
board=custom

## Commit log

2023-06-19 Add top-level gitignore
2023-06-19 Update README, block diagrams, schem. Begin layout
2023-06-25 Add fabrication files
2023-07-02 Antenna imped match files, boilerplate STM code
2023-07-02 Update README and add License files
2023-07-04 Clean up files, add much new code
2023-09-01 More work, esp on firmware

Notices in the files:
Antenna_Impedance_Match/Antenna_Impedance_Match.kicad_pcb:
(C) 2023 ADAM CORDINGLEY
